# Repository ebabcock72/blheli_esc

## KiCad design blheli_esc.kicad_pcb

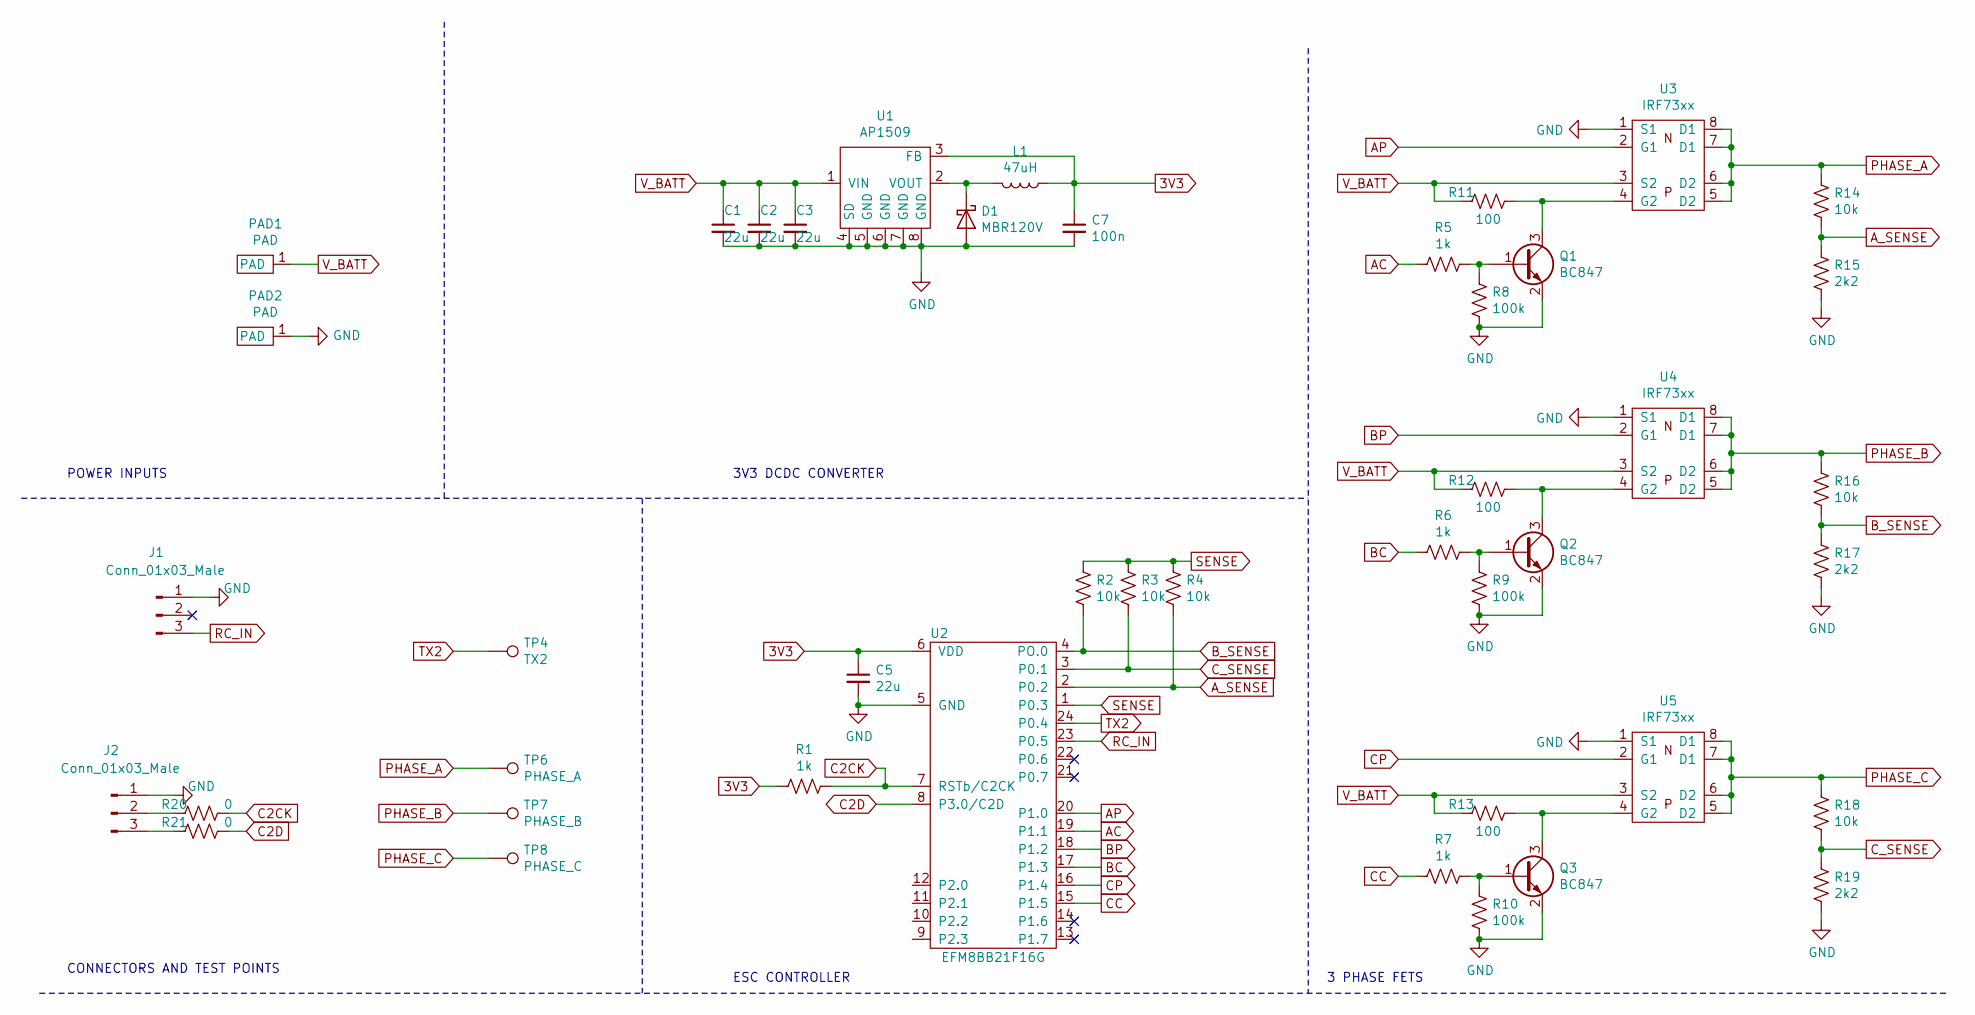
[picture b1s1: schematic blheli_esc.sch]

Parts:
C1, C2, C3, C5: 22u; C_0603_1608Metric
C7: 100n; C_0603_1608Metric
D1: MBR120V; D_SOD-123F
J1, J2: Conn_01x03_Male; PinHeader_1x03_P2.54mm_Vertical
L1: 47uH; inductor_3x3mm
PAD1, PAD2: PAD; TestPoint_Pad_3.0x3.0mm
Q1, Q2, Q3: BC847; SOT-23
R1, R5, R6, R7: 1k; R_0603_1608Metric
R2, R3, R4, R14, R16, R18: 10k; R_0603_1608Metric
R8, R9, R10: 100k; R_0603_1608Metric
R11, R12, R13: 100; R_0603_1608Metric
R15, R17, R19: 2k2; R_0603_1608Metric
R20, R21: 0; R_0603_1608Metric
TP4: TX2; TestPoint_THTPad_D1.0mm_Drill0.5mm
TP6: PHASE_A; TestPoint_Pad_3.0x3.0mm
TP7: PHASE_B; TestPoint_Pad_3.0x3.0mm
TP8: PHASE_C; TestPoint_Pad_3.0x3.0mm
U1: AP1509; AP1509_SO-8
U2: EFM8BB21F16G; efm8b21-qsop24
U3, U4, U5: IRF73xx; IRF7317PbF

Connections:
3V3: C5.1, C7.1, L1.1, R1.2, U1.3 (FB), U2.6 (VDD)
AC: R5.2, U2.19 (P1.1)
AP: U2.20 (P1.0), U3.2 (G1)
A_SENSE: R4.1, R14.1, R15.2, U2.2 (P0.2)
BC: R6.2, U2.17 (P1.3)
BP: U2.18 (P1.2), U4.2 (G1)
B_SENSE: R2.1, R16.1, R17.2, U2.4 (PO.0)
C2CK: R1.1, R20.1, U2.7 (RSTb/C2CK)
C2D: R21.1, U2.8 (P3.0/C2D)
CC: R7.2, U2.15 (P1.5)
CP: U2.16 (P1.4), U5.2 (G1)
C_SENSE: R3.1, R18.1, R19.2, U2.3 (P0.1)
GND: C1.2, C2.2, C3.2, C5.2, C7.2, D1.2 (A), J1.1, J2.1, PAD2.1, Q1.2 (E), Q2.2 (E), Q3.2 (E), R8.1, R9.1, R10.1, R15.1, R17.1, R19.1, U1.4 (SD), U1.5 (GND), U1.6 (GND), U1.7 (GND), U1.8 (GND), U2.5 (GND), U3.1 (S1), U4.1 (S1), U5.1 (S1)
unnamed: D1.1 (K), L1.2, U1.2 (VOUT)
unnamed: J2.2, R20.2
unnamed: J2.3, R21.2
unnamed: Q1.1 (B), R5.1, R8.2
unnamed: Q1.3 (C), R11.1, U3.4 (G2)
unnamed: Q2.1 (B), R6.1, R9.2
unnamed: Q2.3 (C), R12.1, U4.4 (G2)
unnamed: Q3.1 (B), R7.1, R10.2
unnamed: Q3.3 (C), R13.1, U5.4 (G2)
PHASE_A: R14.2, TP6.1, U3.5 (D2), U3.6 (D2), U3.7 (D1), U3.8 (D1)
PHASE_B: R16.2, TP7.1, U4.5 (D2), U4.6 (D2), U4.7 (D1), U4.8 (D1)
PHASE_C: R18.2, TP8.1, U5.5 (D2), U5.6 (D2), U5.7 (D1), U5.8 (D1)
RC_IN: J1.3, U2.23 (P0.5)
SENSE: R2.2, R3.2, R4.2, U2.1 (P0.3)
TX2: TP4.1, U2.24 (P0.4)
V_BATT: C1.1, C2.1, C3.1, PAD1.1, R11.2, R12.2, R13.2, U1.1 (VIN), U3.3 (S2), U4.3 (S2), U5.3 (S2)

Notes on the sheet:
POWER INPUTS
3V3 DCDC CONVERTER
ESC CONTROLLER
CONNECTORS AND TEST POINTS
3 PHASE FETS

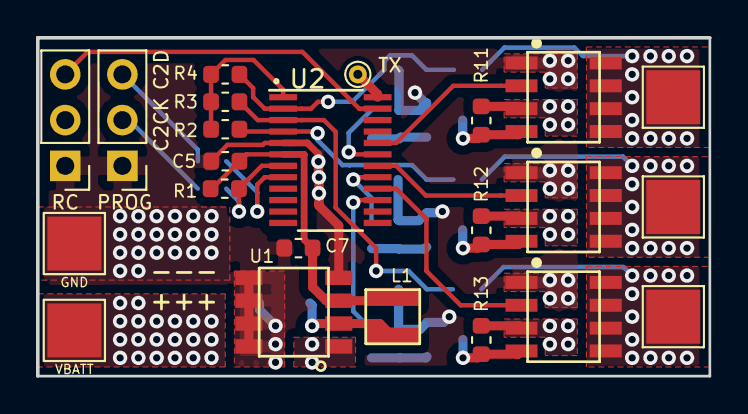
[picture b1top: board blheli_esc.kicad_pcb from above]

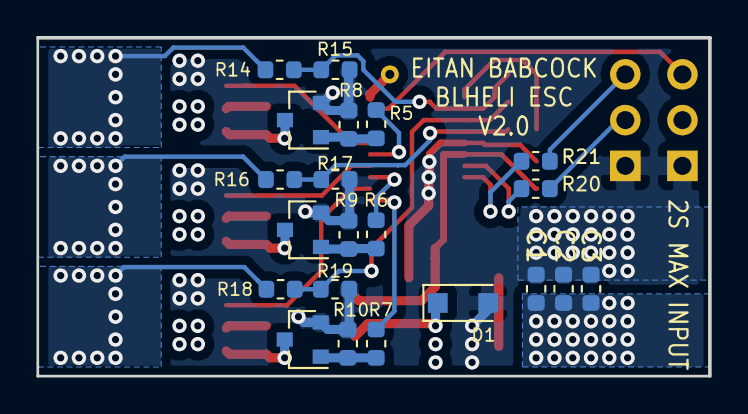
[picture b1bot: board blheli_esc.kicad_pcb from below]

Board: 4 copper layers, 37.3 x 18.8 mm, 44 parts (21 on the bottom side), 29 nets.

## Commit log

2018-12-31 empty project
2019-01-01 schematic mostly done, working on layout
2019-01-02 first draft complete
2019-01-02 added gitignore
2019-01-02 finished layout with moved vbatt
2019-01-20 pdf schematic added to repo
2019-03-02 fixed voltage divider bug
2019-03-02 new design with easier to solder fets. 4 layer board
2019-03-03 small tweaks to layout
2019-03-03 added hex file to repo
